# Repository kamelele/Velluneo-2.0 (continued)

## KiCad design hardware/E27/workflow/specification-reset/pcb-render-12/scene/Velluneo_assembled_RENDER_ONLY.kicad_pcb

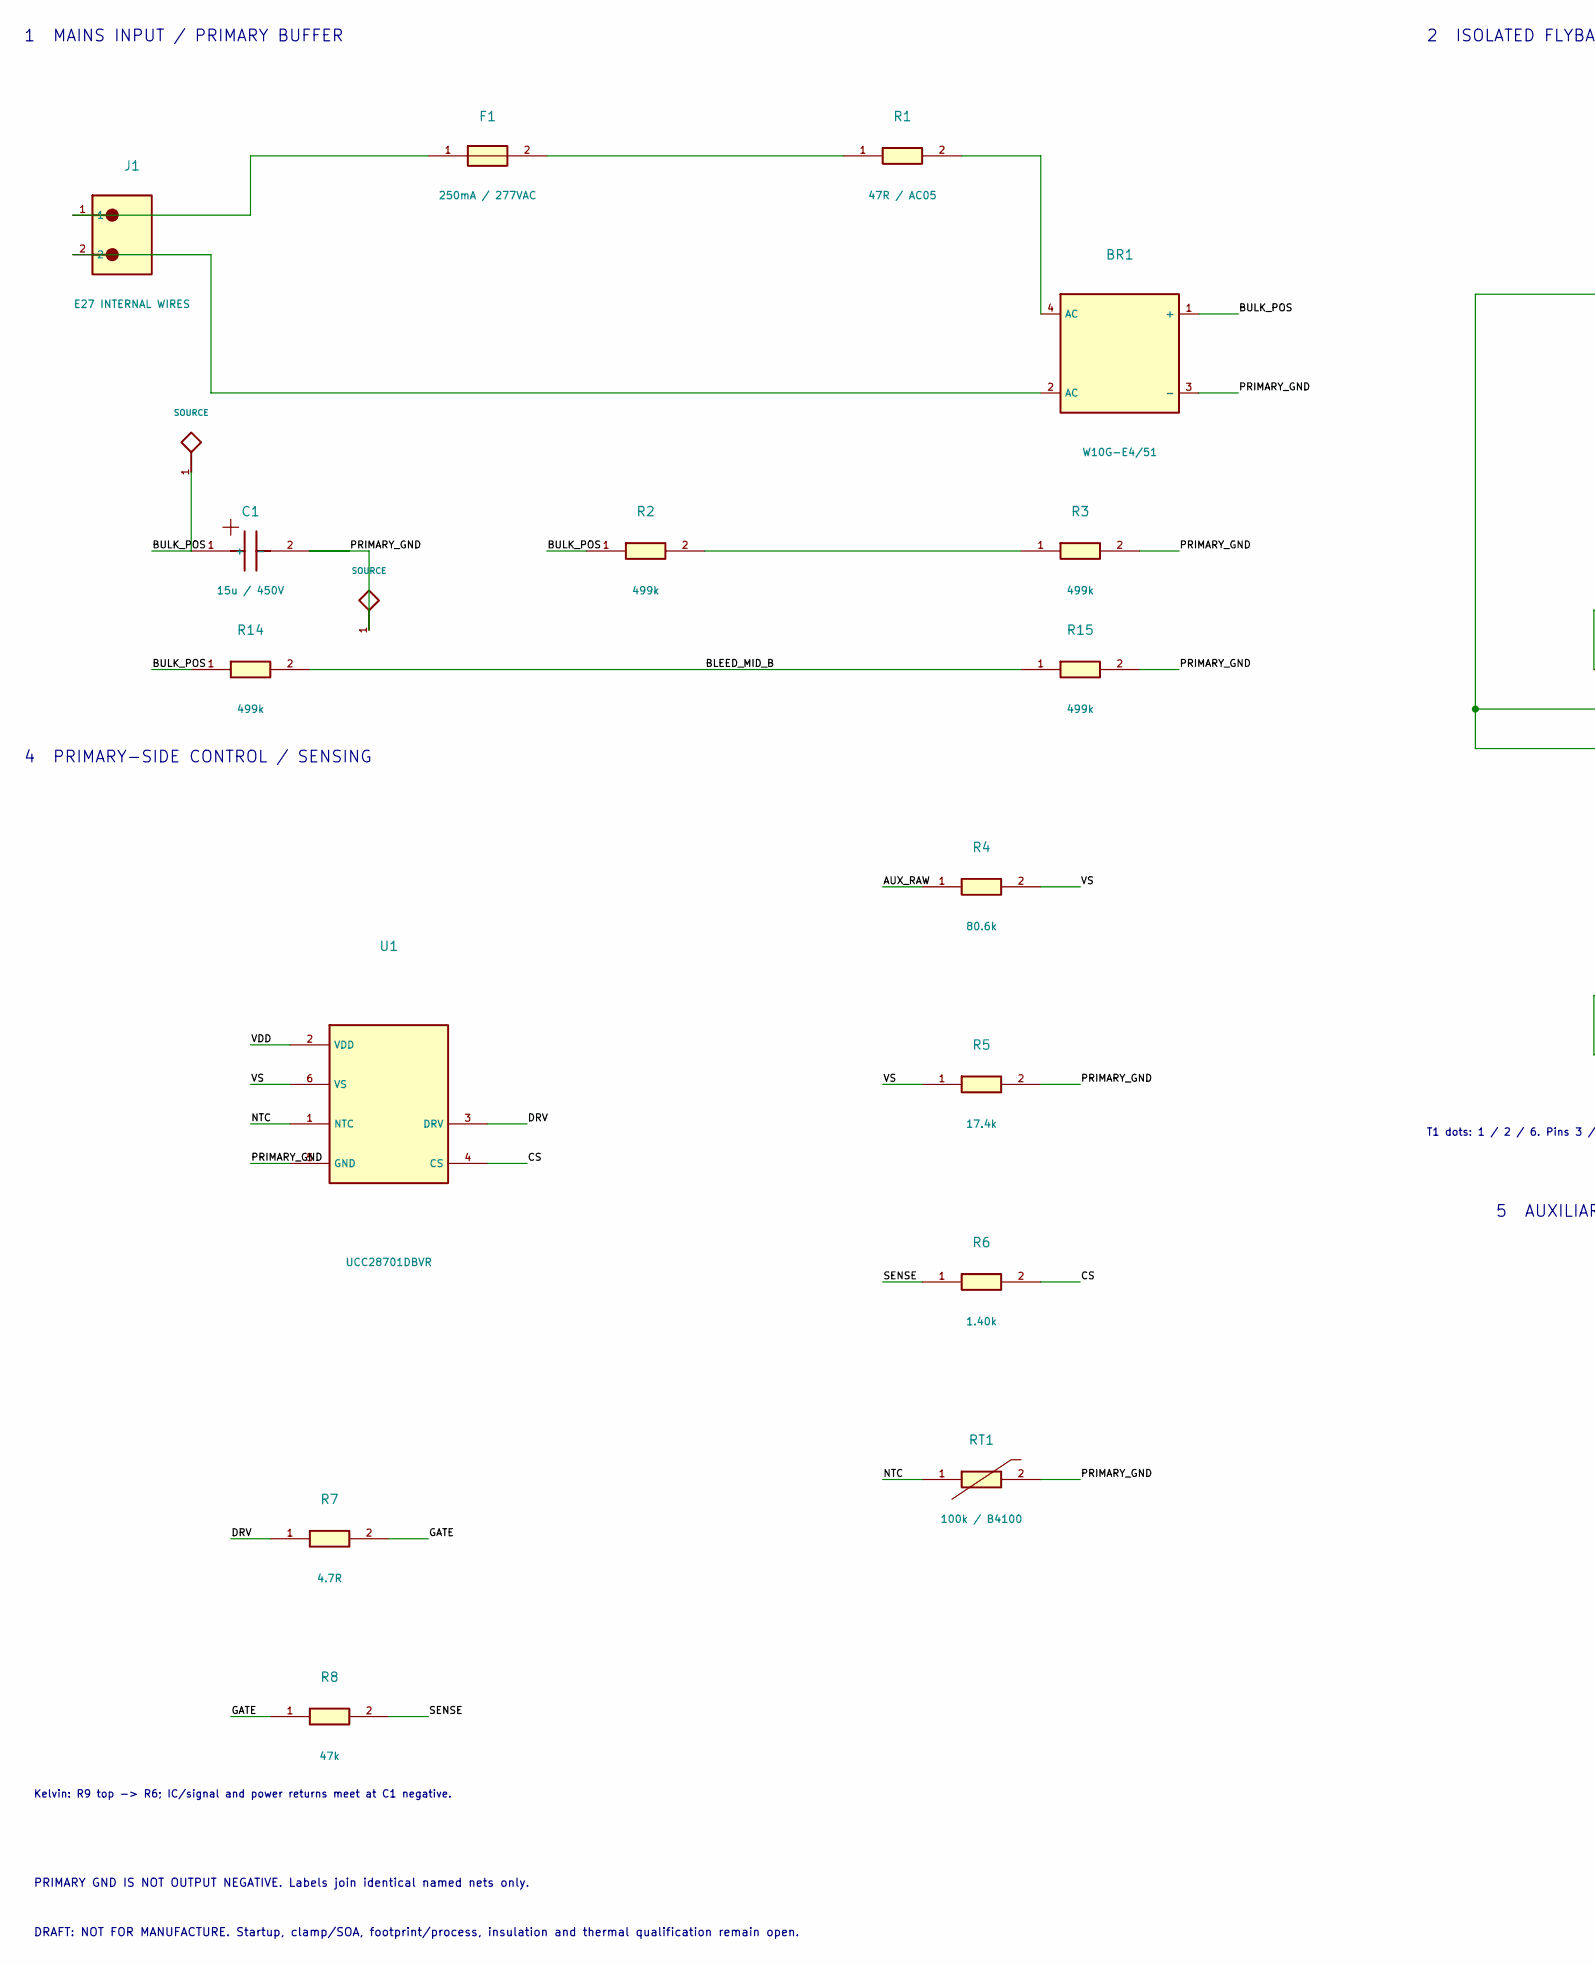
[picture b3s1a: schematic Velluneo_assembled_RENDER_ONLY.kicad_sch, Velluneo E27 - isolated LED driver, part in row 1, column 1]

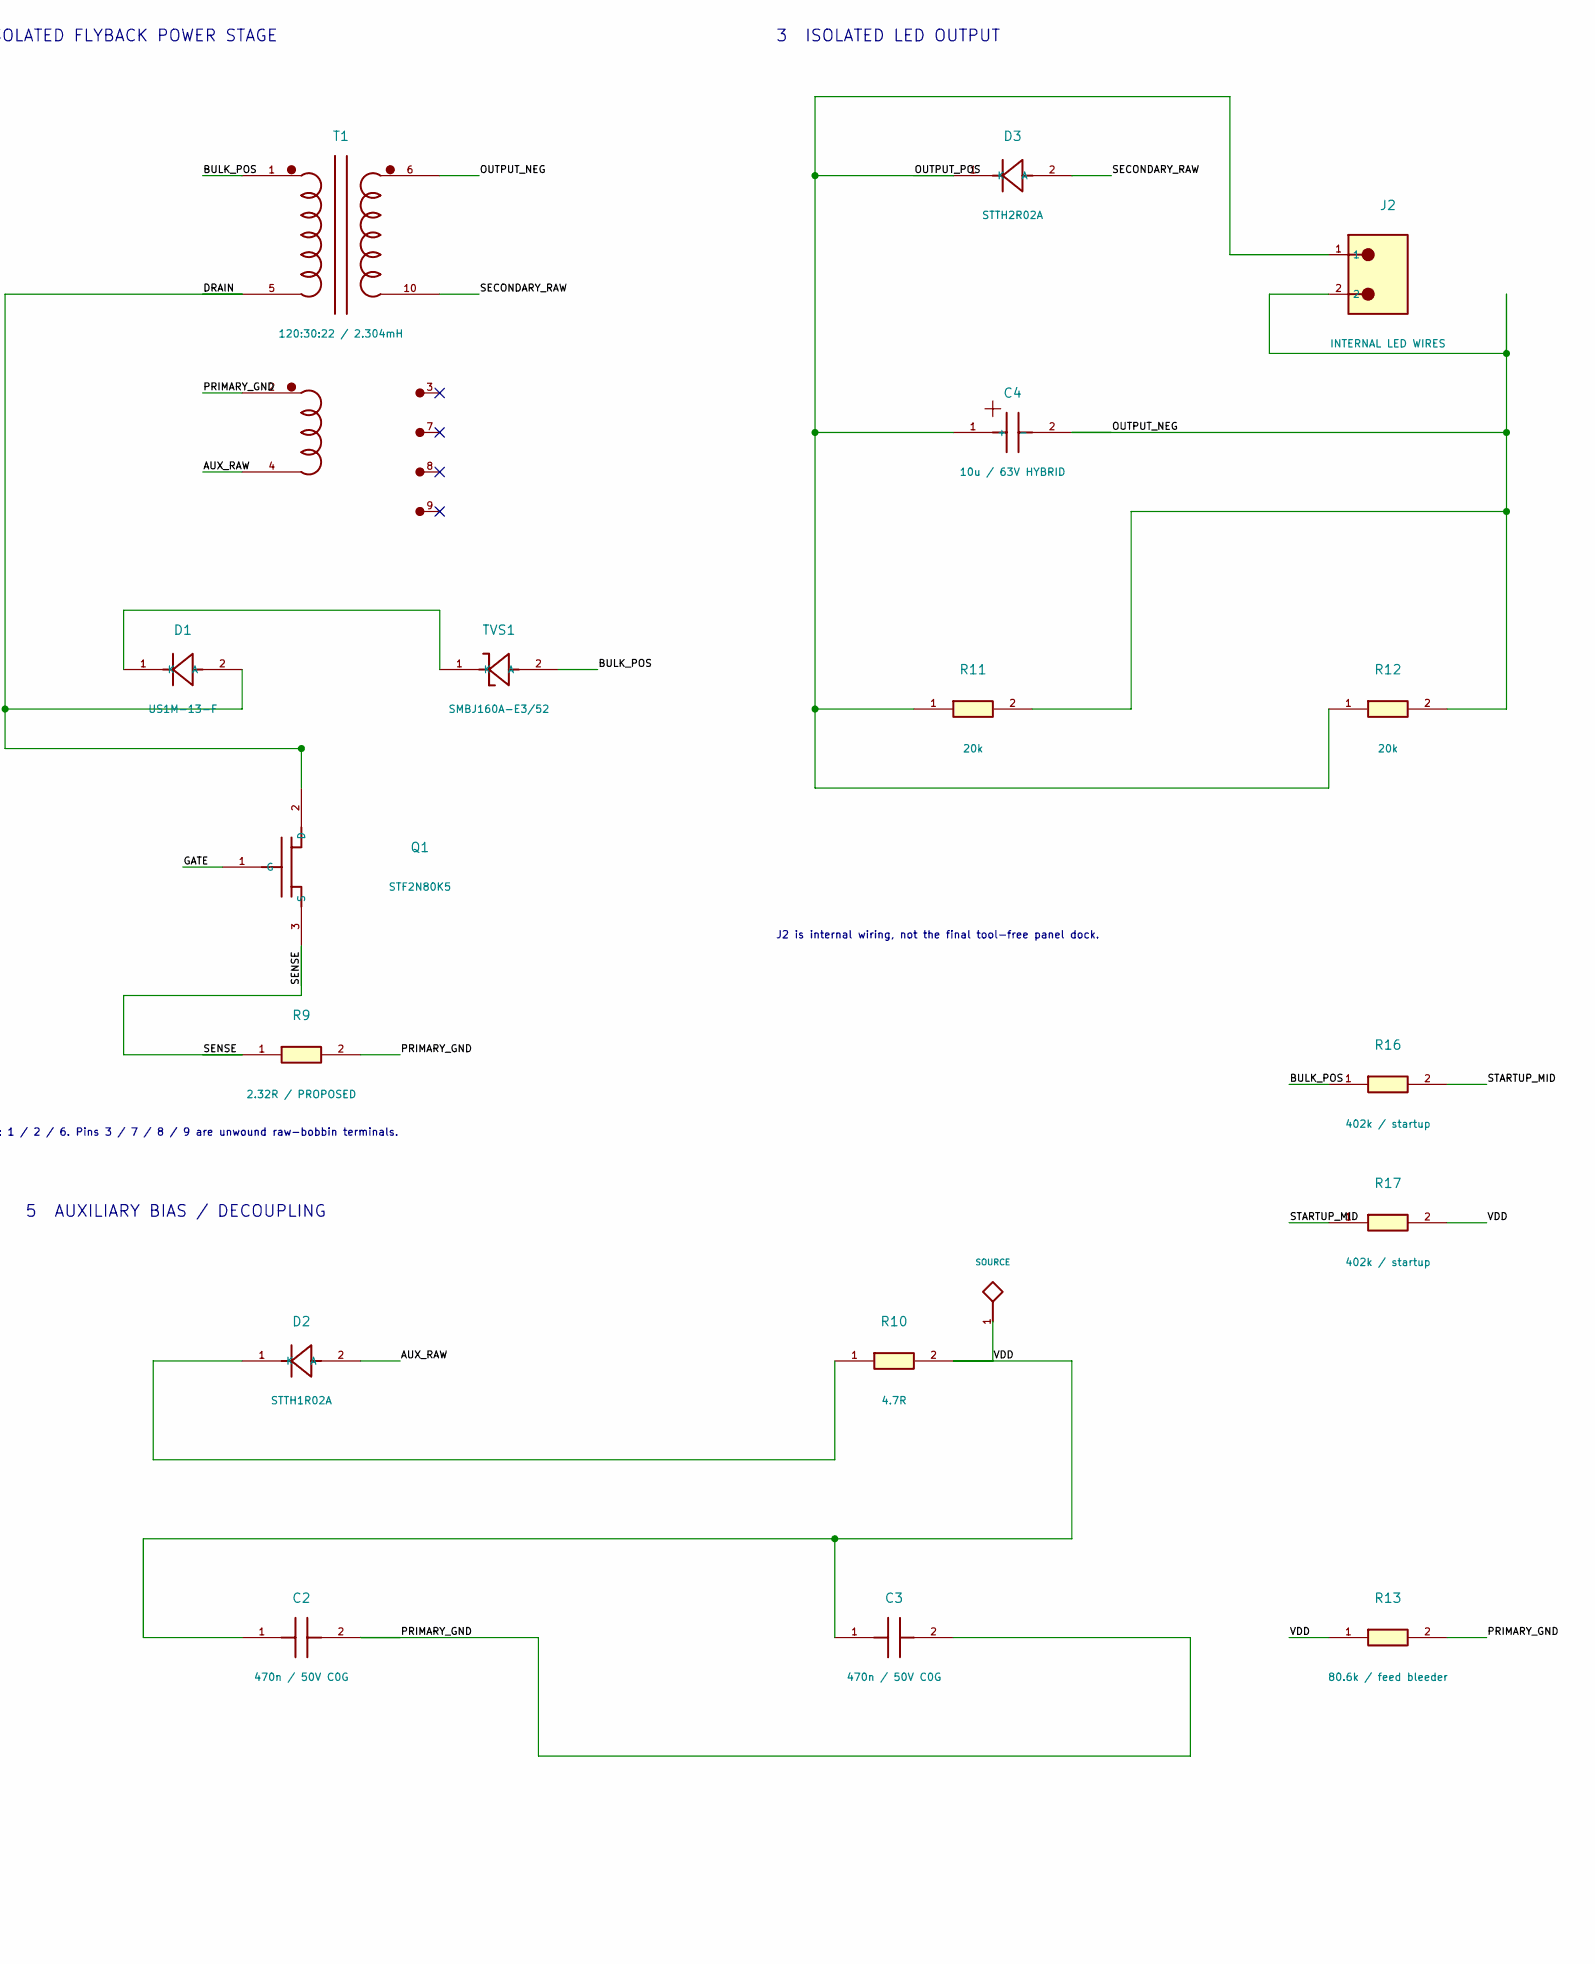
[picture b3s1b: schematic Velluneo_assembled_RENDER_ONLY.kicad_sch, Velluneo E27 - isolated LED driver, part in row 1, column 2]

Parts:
BR1: W10G-E4/51; W10G_Formed5p5_PROJECT; MPN W10G-E4/51
C1: 15u / 450V; Rubycon_BXW_D10_P5_PROJECT_CANDIDATE; MPN 450BXW15MEFR10X20
C2, C3: 470n / 50V C0G; KEMET_2220_C0G_DensityB_Native; MPN C2220C474J5GACTU
C4: 10u / 63V HYBRID; Panasonic_ZA_D_Standard_Native; MPN EEHZA1J100P
D1: US1M-13-F; Diodes_US1M_SMA_Native; MPN US1M-13-F
D2: STTH1R02A; ST_STTH_SMA_Native; MPN STTH1R02A
D3: STTH2R02A; ST_STTH_SMA_Native; MPN STTH2R02A
F1: 250mA / 277VAC; SCHURTER_UMTH_WEB_PROVISIONAL; MPN 3403.0268.23
J1: E27 INTERNAL WIRES; InternalWirePair_P7p62_D1p6_PROJECT_CANDIDATE; MPN PROJECT:INSULATED_INPUT_WIRE_PADS
J2: INTERNAL LED WIRES; InternalWirePair_P7p62_D1p6_PROJECT_CANDIDATE; MPN PROJECT:INSULATED_OUTPUT_WIRE_PADS
Q1: STF2N80K5; STF2N80K5_Stagger5p08_Pad2p25_PROJECT; MPN STF2N80K5
R1: 47R / AC05; AC05_P25p4_FORMED_PROJECT_CANDIDATE; MPN AC05000004709JAC00
R2, R3, R15: 499k; CRCW_2512_NativeReflow; MPN CRCW2512499KFKEG
R4: 80.6k; CRCW_0805_NativeReflow; MPN CRCW080580K6FKEA
R5: 17.4k; CRCW_0805_NativeReflow; MPN CRCW080517K4FKEA
R6: 1.40k; CRCW_0603_NativeReflow; MPN CRCW06031K40FKEA
R7: 4.7R; CRCW_0805_NativeReflow; MPN CRCW08054R70FKEA
R8: 47k; CRCW_0603_NativeReflow; MPN CRCW060347K0FKEA
R9: 2.32R / PROPOSED; CRCW_1206_NativeReflow; MPN CRCW12062R32FKEA
R10: 4.7R; CRCW_2512_NativeReflow; MPN CRCW25124R70FKEG
R11, R12: 20k; CRCW_2512_NativeReflow; MPN CRCW251220K0FKEG
R13: 80.6k / feed bleeder; CRCW_0603_NativeReflow; MPN CRCW060380K6FKEA
R14: 499k; CRCW_2512_R14_SilkClear; MPN CRCW2512499KFKEG
R16, R17: 402k / startup; CRCW_2512_NativeReflow; MPN CRCW2512402KFKEG
RT1: 100k / B4100; NTCS0603_NativeReflow; MPN NTCS0603E3104FXT
T1: 120:30:22 / 2.304mH; TDK_EFD25_Pad2p0_PROJECT; MPN CUSTOM:EFD25_120_30_22
TVS1: SMBJ160A-E3/52; Vishay_SMBJ_PROJECT_CANDIDATE; MPN SMBJ160A-E3/52
U1: UCC28701DBVR; UCC28701_DBV_Native; MPN UCC28701DBVR

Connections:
/AUX_RAW: D2.2 (A), R4.1, T1.4
/BLEED_MID_B: R14.2, R15.1
/BULK_POS: BR1.1 (+), C1.1 (+), R2.1, R14.1, R16.1, T1.1, TVS1.2 (A)
/CS: R6.2, U1.4 (CS)
/DRAIN: D1.2 (A), Q1.2 (D), T1.5
/DRV: R7.1, U1.3 (DRV)
/GATE: Q1.1 (G), R7.2, R8.1
/NTC: RT1.1, U1.1 (NTC)
/OUTPUT_NEG: C4.2 (-), J2.2, R11.2, R12.2, T1.6
/OUTPUT_POS: C4.1 (+), D3.1 (K), J2.1, R11.1, R12.1
/PRIMARY_GND: BR1.3 (-), C1.2 (-), C2.2, C3.2, R3.2, R5.2, R9.2, R13.2, R15.2, RT1.2, T1.2, U1.5 (GND)
/SECONDARY_RAW: D3.2 (A), T1.10
/SENSE: Q1.3 (S), R6.1, R8.2, R9.1
/STARTUP_MID: R16.2, R17.1
/VDD: C2.1, C3.1, R10.2, R13.1, R17.2, U1.2 (VDD)
/VS: R4.2, R5.1, U1.6 (VS)
unnamed: BR1.2 (AC), J1.2
unnamed: BR1.4 (AC), R1.2
unnamed: D1.1 (K), TVS1.1 (K)
unnamed: D2.1 (K), R10.1
unnamed: F1.1, J1.1
unnamed: F1.2, R1.1
unnamed: R2.2, R3.1

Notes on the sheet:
1 MAINS INPUT / PRIMARY BUFFER
2 ISOLATED FLYBACK POWER STAGE
3 ISOLATED LED OUTPUT
4 PRIMARY-SIDE CONTROL / SENSING
5 AUXILIARY BIAS / DECOUPLING
PRIMARY GND IS NOT OUTPUT NEGATIVE. Labels join identical named nets only.
DRAFT: NOT FOR MANUFACTURE. Startup, clamp/SOA, footprint/process, insulation and thermal qualification remain open.
T1 dots: 1 / 2 / 6. Pins 3 / 7 / 8 / 9 are unwound raw-bobbin terminals.
J2 is internal wiring, not the final tool-free panel dock.
Kelvin: R9 top -> R6; IC/signal and power returns meet at C1 negative.

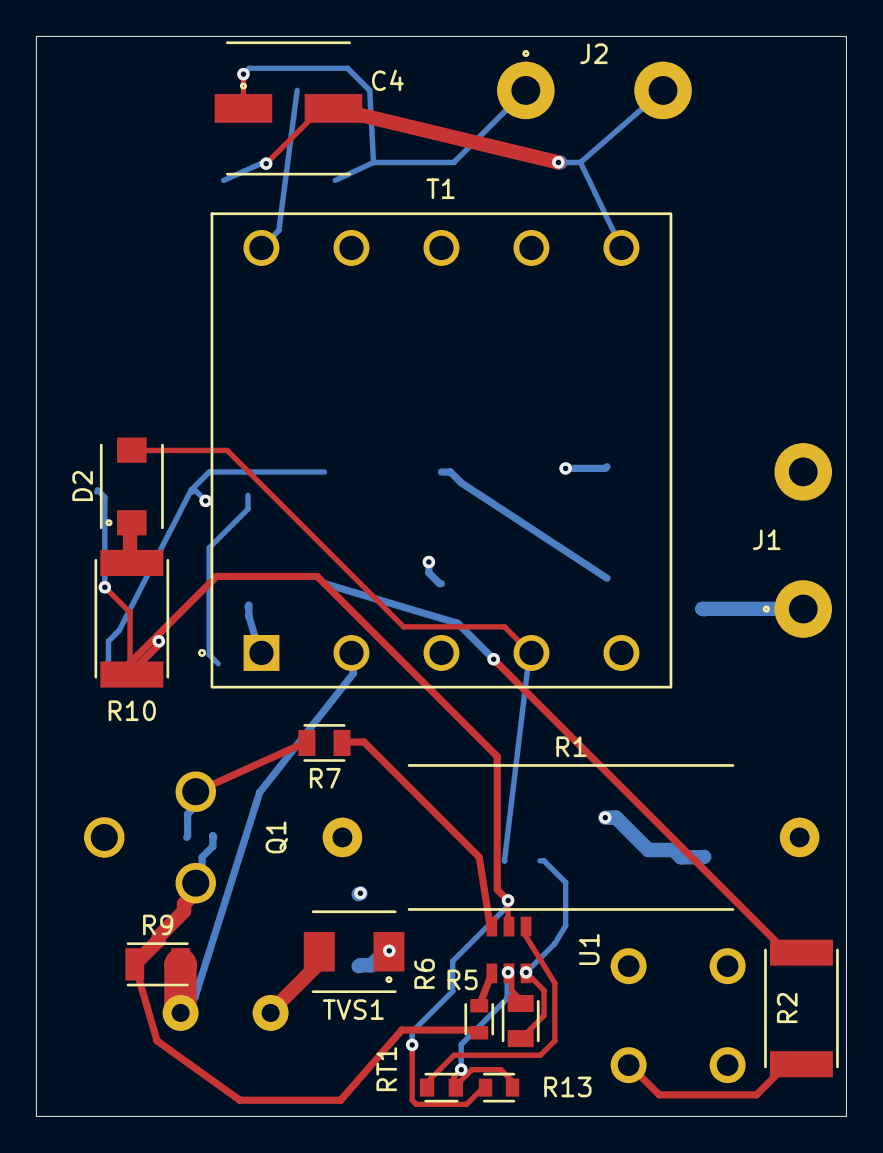
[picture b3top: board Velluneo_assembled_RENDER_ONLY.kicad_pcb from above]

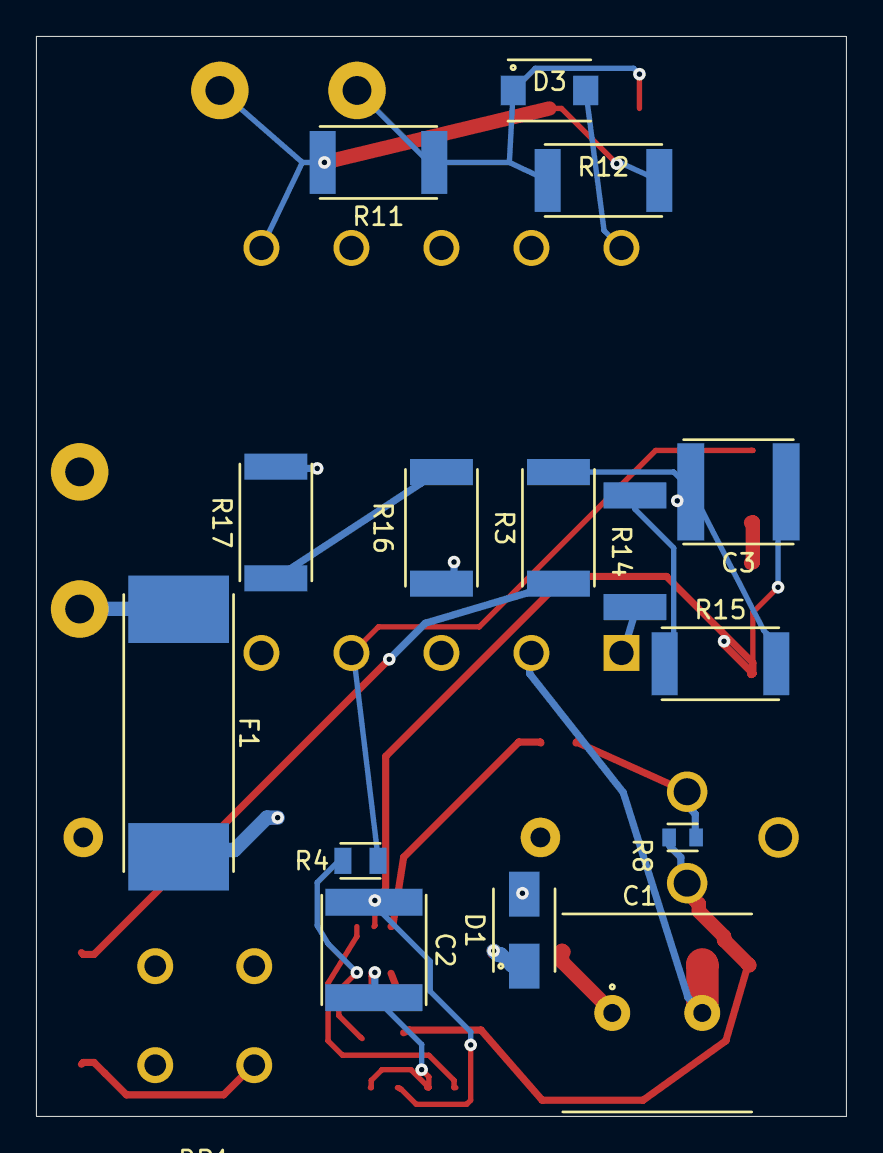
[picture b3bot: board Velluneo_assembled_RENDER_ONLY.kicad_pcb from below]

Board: 4 copper layers, 45.0 x 60.0 mm, 33 parts (16 on the bottom side), 23 nets.
